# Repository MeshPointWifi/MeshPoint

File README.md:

# MeshPoint
MeshPoint is Open source Wifi Hotspot for Crisis Situations
www.meshpointone.com

## MeshPoint v4.1

## Technical Specifications

- **CPU / SoC:** 700 MHz Quad-core Cortex-A7 / Qualcomm IPQ4018
- **RAM memory and storage:** 128 MB NAND and 8 MB NOR flash, 256 MB DDR3 RAM
- **Wi-Fi standards:** 802.11 a/b/g/n/ac Wave 2
- **Mesh protocol:** 802.11s mesh networking protocol
- **Radio:** 2.4 GHz and 5 GHz dual band
- **MIMO:** 2.4 GHz 2x2 MIMO / 5.8 GHz 2x2 MIMO
- **VLAN:** 802.1Q VLAN
- **Monitoring:** SNMP v2 / SNMP v3
- **Environment:** Indoor / Outdoor
- **Concurrent clients:** 300+
- **PoE mode:** Passive PoE in and PoE out
- **Power supply:** Battery powered, solar powered or PoE in
- **Antennas:** Internal dual-band antennas, 7 dBi
- **Wireless security:** WEP, WPA-PSK, WPA-Enterprise (WPA/WPA2, TKIP/AES), WPA3
- **Power consumption:** Average 4 W, maximum 12 W
- **Maximum TX power:** 20 dBm
- **Operating temperature:** -40 °C to 70 °C (-40 °F to 158 °F)
- **Licence:** Free
- **Available interfaces:** USB 2.0, USB 3.0, I2C, I2S, TDM, SPI, UART, GPIO, JTAG
- **Network ports:** 2x 1000BASE-T Ethernet ports
- **LTE modem option:** USB LTE Cat 4 modem

## New features

- [x] PoE Passtrough ( IN + OUT - daisy-chain )
- [x] On board sensor PRESSURE HUMIDITY TEMP
- [x] PCF8563T - on board RTC

## Licence

This project (hardware designs, 3D files and documentation) is released under the
**CERN Open Hardware Licence Version 2 - Strongly Reciprocal (CERN-OHL-S v2)**.

See the [LICENCE](LICENCE) file for the full text.
More info: https://cern-ohl.web.cern.ch/

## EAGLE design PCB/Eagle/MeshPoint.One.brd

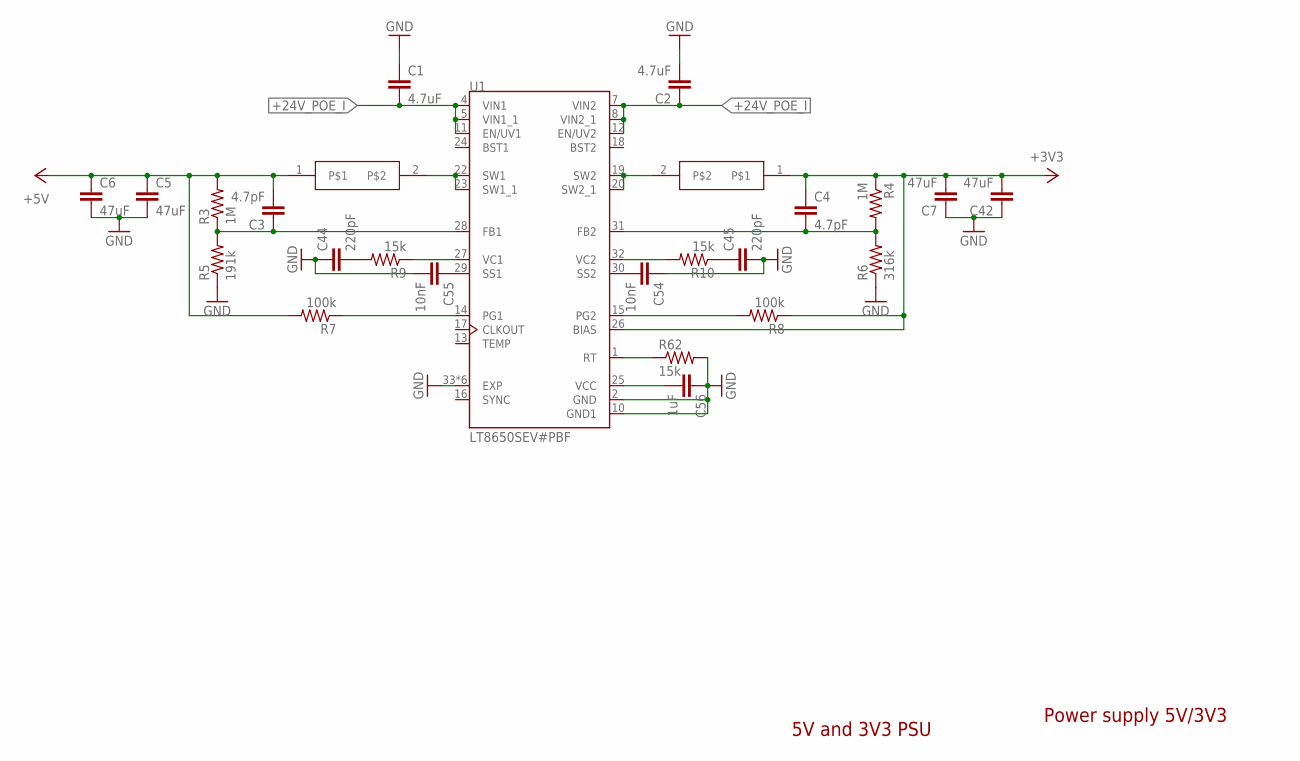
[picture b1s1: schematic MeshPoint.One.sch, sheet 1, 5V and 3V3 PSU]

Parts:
C1, C2: 4.7uF; C1206
C3, C4: 4.7pF; C0402
C5, C6, C7, C42: 47uF; C1206
C44, C45: 220pF; C0402
C54, C55: 10nF; C0402
C56: 1uF; C0402
L1, L2: PA4333.102NLTPA4333.102NLT; INDC6932X320
R3, R4: 1M; R0402
R5: 191k; R0402
R6: 316k; R0402
R7, R8: 100k; R0402
R9, R10, R62: 15k; R0402
U1: LT8650SEV#PBF; QFN50P600X400X103-32N240X440

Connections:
+24V_POE_I: C1.2, C2.1, U1.4 (VIN1), U1.5 (VIN1_1), U1.7 (VIN2), U1.8 (VIN2_1), U1.11 (EN/UV1), U1.12 (EN/UV2); also elsewhere on the board
GND: C1.1, C2.2, C5.2, C6.2, C7.1, C42.1, C44.1, C45.2, C54.1, C55.2, C56.1, R5.1, R6.1, R62.2, U1.2 (GND), U1.10 (GND1), U1.33 (EXP), U1.34 (EXP), U1.35 (EXP), U1.36 (EXP), U1.37 (EXP), U1.38 (EXP); also elsewhere on the board
unnamed: L1.2, U1.22 (SW1), U1.23 (SW1_1)
unnamed: L2.2, U1.19 (SW2), U1.20 (SW2_1)
unnamed: C3.1, R3.1, R5.2, U1.28 (FB1)
unnamed: C4.2, R4.2, R6.2, U1.31 (FB2)
unnamed: C55.1, U1.29 (SS1)
unnamed: R7.1, U1.14 (PG1)
unnamed: R8.2, U1.15 (PG2)
unnamed: C54.2, U1.30 (SS2)
unnamed: C44.2, R9.2
unnamed: C45.1, R10.1
unnamed: R9.1, U1.27 (VC1)
unnamed: R10.2, U1.32 (VC2)
unnamed: R62.1, U1.1 (RT)
unnamed: C56.2, U1.25 (VCC)
unnamed 153: C4.1, C7.2, C42.2, L2.1, R4.1, R8.1, U1.26 (BIAS); also elsewhere on the board
unnamed 184: C3.2, C5.1, C6.1, L1.1, R3.2, R7.2; also elsewhere on the board

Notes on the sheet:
Power supply 5V/3V3
5V and 3V3 PSU

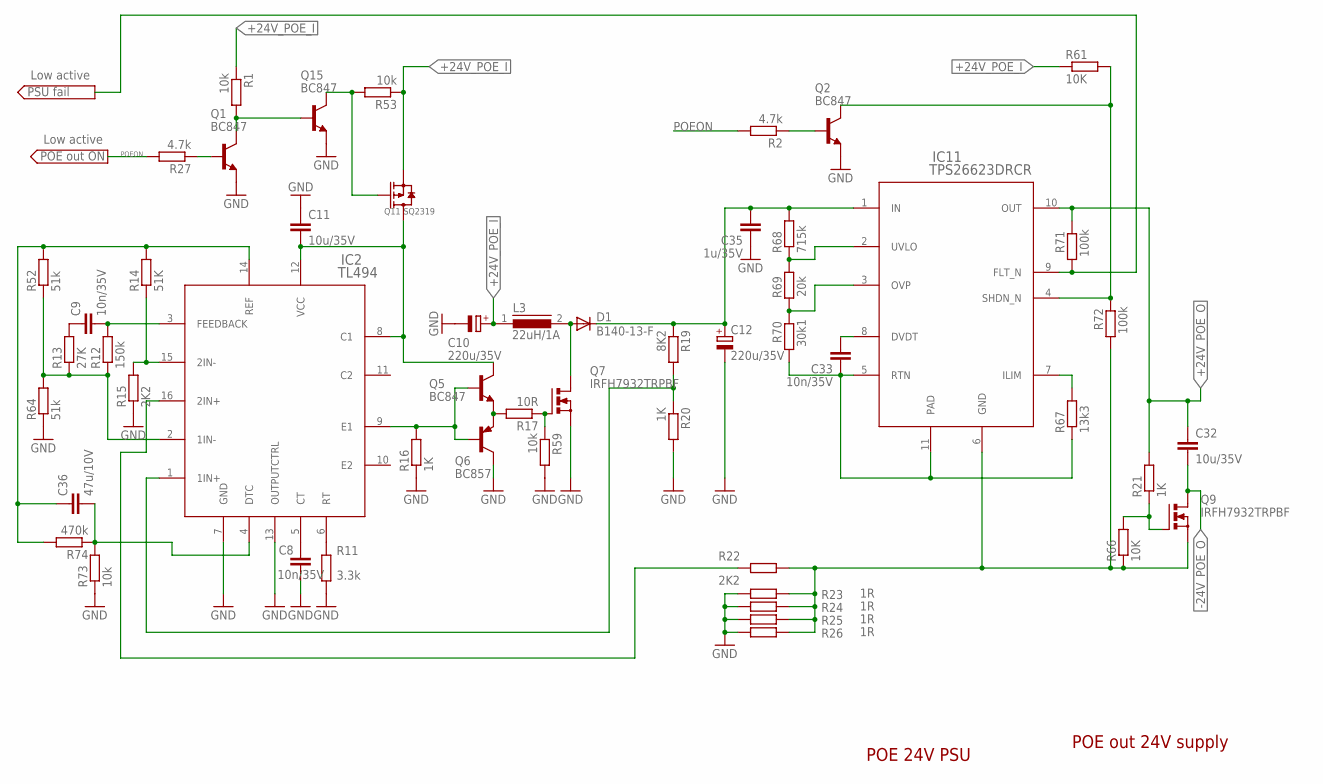
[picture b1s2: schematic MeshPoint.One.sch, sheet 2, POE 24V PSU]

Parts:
C8, C9, C33: 10n/35V; C0402
C10, C12: 220u/35V; 153CLV-1010
C11, C32: 10u/35V; C1206
C35: 1u/35V; C0402
C36: 47u/10V; C1206
D1: B140-13-F; SMB
IC2: TL494; PW16
IC11: TPS26623DRCR; DRC0010J
L3: 22uH/1A; DR125
Q1, Q2, Q5, Q15: BC847; SOT23
Q6: BC857; SOT23-BEC
Q7, Q9: IRFH7932TRPBF; PG-TDSON-8
Q11: SQ2319; SOT-23:1
R1, R53, R59, R73: 10k; R0402
R2, R27: 4.7k; R0402
R11: 3.3k; R0402
R12: 150k; R0402
R13: 27K; R0402
R14: 51K; R0402
R15, R22: 2K2; R0402
R16, R20, R21: 1K; R0402
R17: 10R; R0402
R19: 8K2; R0402
R23, R24, R25, R26: 1R; M1206
R52, R64: 51k; R0402
R61, R66: 10K; R0402
R67: 13k3; R0402
R68: 715k; R0402
R69: 20k; R0402
R70: 30k1; R0402
R71, R72: 100k; R0402
R74: 470k; R0402

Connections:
+24V_POE_I: C10.+, L3.1, Q11.2 (S), R1.1, R53.1, R61.1; also elsewhere on the board
+24V_POE_O: C32.1, IC11.10 (OUT), R21.2, R71.2; also elsewhere on the board
-24V_POE_O: C32.2, Q9.5 (D), Q9.6 (D), Q9.7 (D), Q9.8 (D), Q9.TH (D); also elsewhere on the board
GND: C8.2, C10.-, C11.1, C12.-, C35.1, IC2.7 (GND), IC2.13 (OUTPUTCTRL), Q1.2 (E), Q2.2 (E), Q6.C, Q7.1 (S), Q7.2 (S), Q7.3 (S), Q15.2 (E), R11.1, R15.1, R16.1, R20.2, R23.1, R24.1, R25.1, R26.1, R59.2, R64.1, R73.1; also elsewhere on the board
unnamed: IC2.6 (RT), R11.2
unnamed: C8.1, IC2.5 (CT)
unnamed: C36.2, IC2.4 (DTC), R73.2, R74.1
unnamed: C9.2, IC2.3 (FEEDBACK), R12.2
unnamed: Q1.1 (B), R27.1
unnamed: IC2.15 (2IN-), R14.1, R15.2
unnamed: IC2.9 (E1), Q5.1 (B), Q6.B, R16.2
unnamed: Q5.2 (E), Q6.E, R17.2
unnamed: C36.1, IC2.14 (REF), R14.2, R52.2, R74.2
unnamed: Q7.4 (G), R17.1, R59.1
unnamed: IC2.1 (1IN+), R19.2, R20.1
unnamed: C33.2, IC11.8 (DVDT)
unnamed: IC2.16 (2IN+), R22.1
unnamed: Q1.3 (C), Q15.1 (B), R1.2
unnamed: Q2.1 (B), R2.1
unnamed: C9.1, R13.2
unnamed: IC11.4 (SHDN_N), Q2.3 (C), R61.2, R72.2
unnamed: C12.+, C35.2, D1.C, IC11.1 (IN), R19.1, R68.2
unnamed: Q11.1 (G), Q15.3 (C), R53.2
unnamed: C11.2, IC2.8 (C1), IC2.12 (VCC), Q5.3 (C), Q11.3 (D)
unnamed: Q9.4 (G), R21.1, R66.2
unnamed: IC11.7 (ILIM), R67.2
unnamed: D1.A, L3.2, Q7.5 (D), Q7.6 (D), Q7.7 (D), Q7.8 (D), Q7.TH (D)
unnamed: C33.1, IC11.5 (RTN), IC11.11 (PAD), R67.1, R70.1
unnamed: IC11.6 (GND), Q9.1 (S), Q9.2 (S), Q9.3 (S), R22.2, R23.2, R24.2, R25.2, R26.2, R66.1, R72.1
unnamed: IC2.2 (1IN-), R12.1, R13.1, R52.1, R64.2
unnamed: IC11.2 (UVLO), R68.1, R69.2
unnamed: IC11.3 (OVP), R69.1, R70.2
POEON: R2.2, R27.2; also elsewhere on the board
PSU_FAIL: IC11.9 (FLT_N), R71.1

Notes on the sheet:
POE out 24V supply
POE 24V PSU
Low active

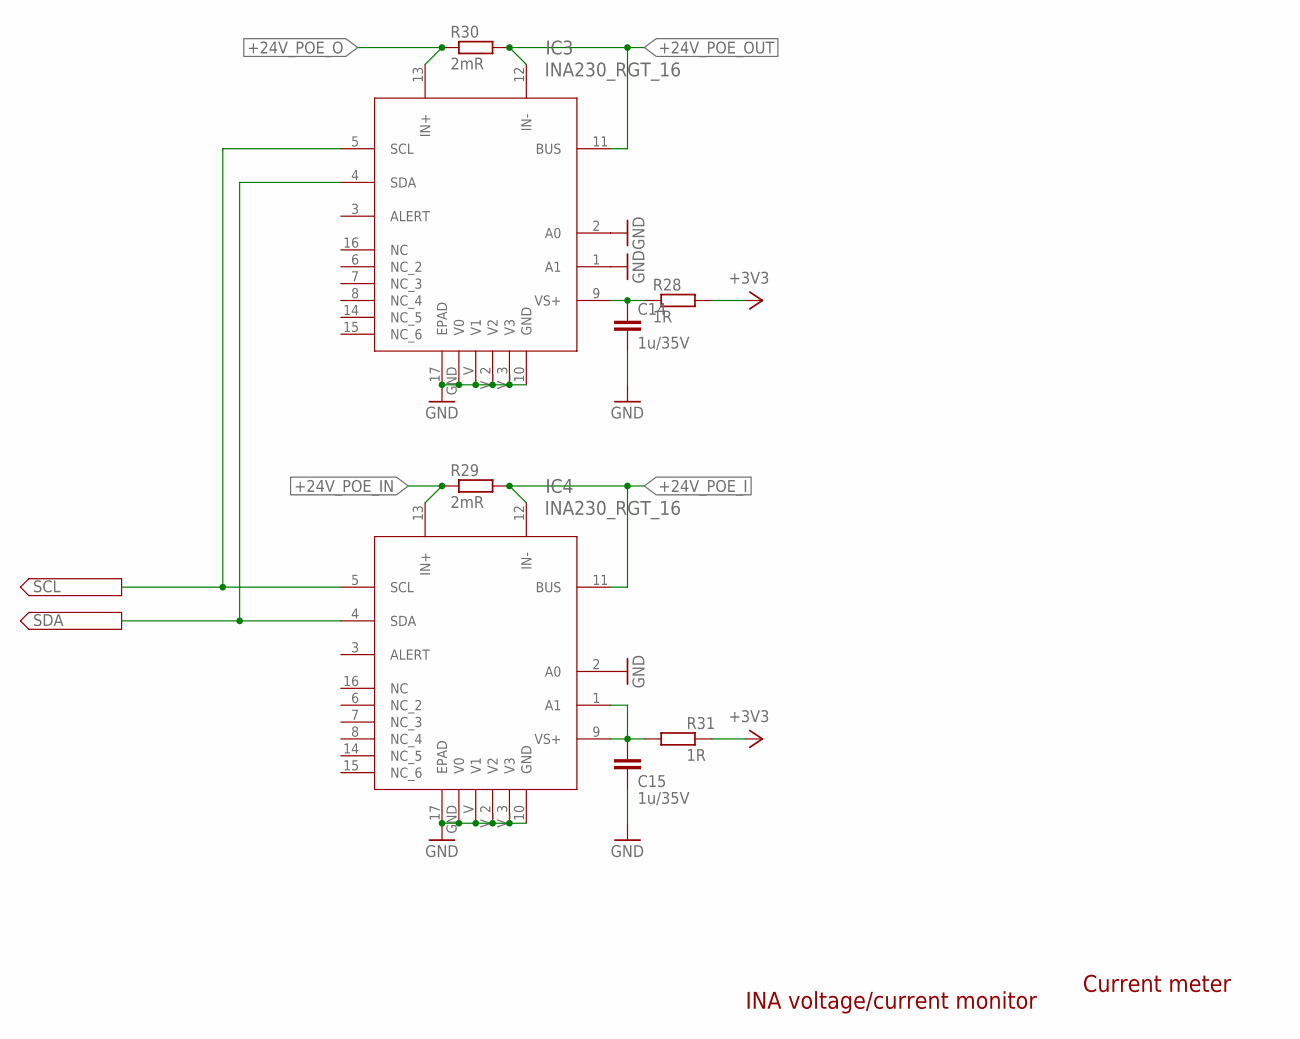
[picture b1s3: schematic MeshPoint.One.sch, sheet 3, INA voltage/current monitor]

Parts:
C14, C15: 1u/35V; C0402
IC3, IC4: INA230_RGT_16; RGT16_1P7X1P7
R28, R31: 1R; R0402
R29, R30: 2mR; M1206

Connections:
+24V_POE_I: IC4.11 (BUS), IC4.12 (IN-), R29.2; also elsewhere on the board
+24V_POE_IN: IC4.13 (IN+), R29.1; also elsewhere on the board
+24V_POE_O: IC3.13 (IN+), R30.1; also elsewhere on the board
+24V_POE_OUT: IC3.11 (BUS), IC3.12 (IN-), R30.2; also elsewhere on the board
GND: C14.2, C15.2, IC3.1 (A1), IC3.2 (A0), IC3.10 (GND), IC3.17 (EPAD), IC3.GND (V0), IC3.V (V1), IC3.V_2 (V2), IC3.V_3 (V3), IC4.2 (A0), IC4.10 (GND), IC4.17 (EPAD), IC4.GND (V0), IC4.V (V1), IC4.V_2 (V2), IC4.V_3 (V3); also elsewhere on the board
unnamed: C14.1, IC3.9 (VS+), R28.1
unnamed: C15.1, IC4.1 (A1), IC4.9 (VS+), R31.1
unnamed 153: R28.2, R31.2; also elsewhere on the board
SCL: IC3.5 (SCL), IC4.5 (SCL); also elsewhere on the board
SDA: IC3.4 (SDA), IC4.4 (SDA); also elsewhere on the board

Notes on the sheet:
Current meter
INA voltage/current monitor

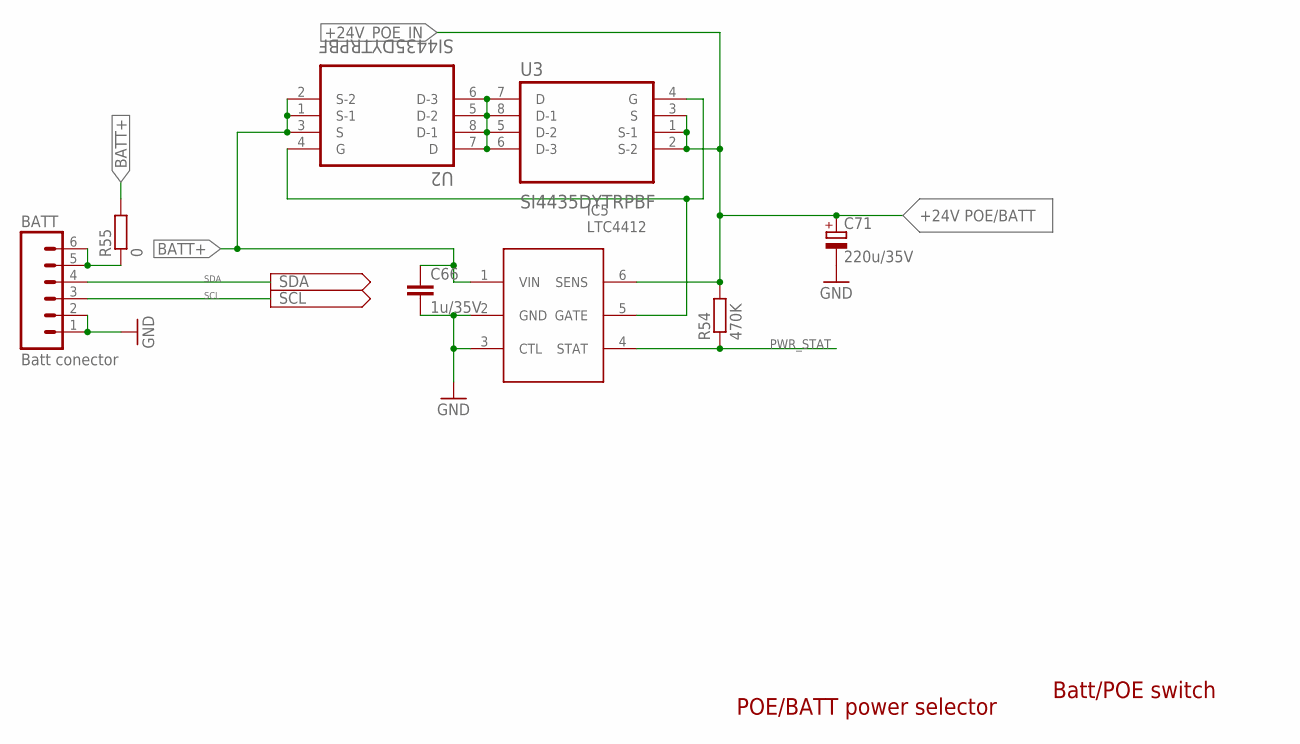
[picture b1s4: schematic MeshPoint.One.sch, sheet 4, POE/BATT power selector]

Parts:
BATT: Batt conector; 06P
C66: 1u/35V; C0402
C71: 220u/35V; 153CLV-1010
IC5: LTC4412; TSOT23
R54: 470K; R0402
R55: 0; M0805
U2, U3: SI4435DYTRPBF; SOIC127P490X600X175-8N

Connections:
+24V_POE_IN: C71.+, IC5.6 (SENS), R54.2, U3.1 (S-1), U3.2 (S-2), U3.3 (S); also elsewhere on the board
BATT+: C66.1, IC5.1 (VIN), R55.2, U2.1 (S-1), U2.2 (S-2), U2.3 (S)
GND: BATT.1, BATT.2, C66.2, C71.-, IC5.2 (GND), IC5.3 (CTL); also elsewhere on the board
unnamed: U2.5 (D-2), U2.6 (D-3), U2.7 (D), U2.8 (D-1), U3.5 (D-2), U3.6 (D-3), U3.7 (D), U3.8 (D-1)
unnamed: IC5.5 (GATE), U2.4 (G), U3.4 (G)
unnamed: BATT.5, BATT.6, R55.1
PWR_STAT: IC5.4 (STAT), R54.1
SCL: BATT.3; also elsewhere on the board
SDA: BATT.4; also elsewhere on the board

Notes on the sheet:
Batt/POE switch
POE/BATT power selector
+24V POE/BATT

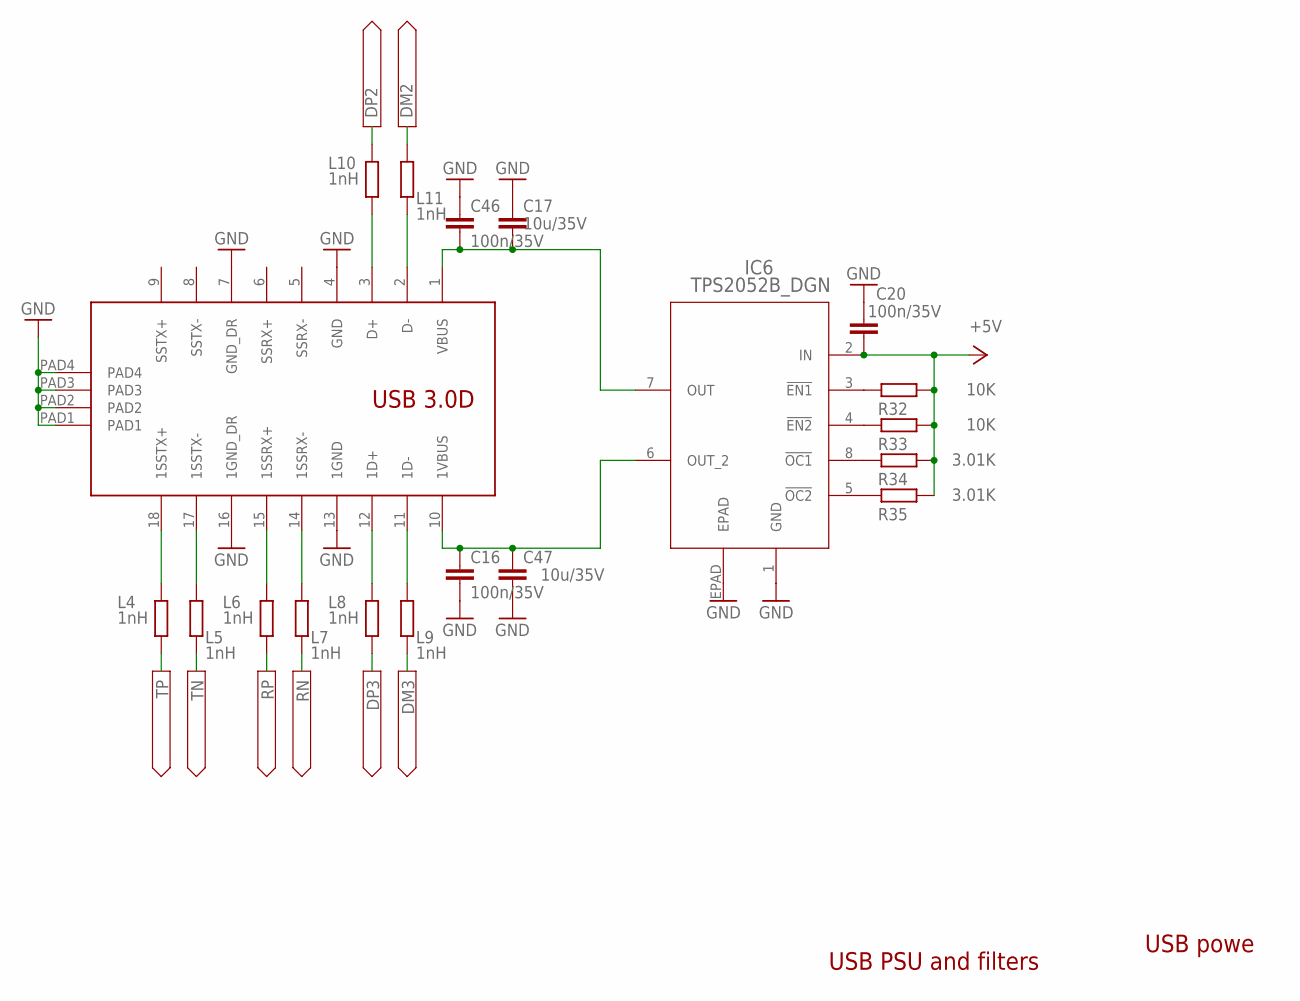
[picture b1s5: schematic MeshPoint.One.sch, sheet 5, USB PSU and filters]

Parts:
C16, C20, C46: 100n/35V; C0402
C17, C47: 10u/35V; C1206
IC6: TPS2052B_DGN; DGN8_1P89X1P57
L4, L5, L6, L7, L8, L9, L10, L11: 1nH; R0402
R32, R33: 10K; R0402
R34, R35: 3.01K; R0402
USB3.0: USB3.0D

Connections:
DM2: L11.1; also elsewhere on the board
DM3: L9.2; also elsewhere on the board
DP2: L10.1; also elsewhere on the board
DP3: L8.2; also elsewhere on the board
GND: C16.2, C17.1, C20.1, C46.1, C47.2, IC6.1 (GND), IC6.EPAD, USB3.0.4 (GND), USB3.0.7 (GND_DR), USB3.0.13 (1GND), USB3.0.16 (1GND_DR), USB3.0.PAD1, USB3.0.PAD2, USB3.0.PAD3, USB3.0.PAD4; also elsewhere on the board
unnamed: L4.1, USB3.0.18 (1SSTX+)
unnamed: L5.1, USB3.0.17 (1SSTX-)
unnamed: L6.1, USB3.0.15 (1SSRX+)
unnamed: L7.1, USB3.0.14 (1SSRX-)
unnamed: L8.1, USB3.0.12 (1D+)
unnamed: L9.1, USB3.0.11 (1D-)
unnamed: IC6.3 (!EN1), R32.2
unnamed: IC6.4 (!EN2), R33.2
unnamed: IC6.8 (!OC1), R34.2
unnamed: IC6.5 (!OC2), R35.2
unnamed: C16.1, C47.1, IC6.6 (OUT_2), USB3.0.10 (1VBUS)
unnamed: L10.2, USB3.0.3 (D+)
unnamed: L11.2, USB3.0.2 (D-)
unnamed: C17.2, C46.2, IC6.7 (OUT), USB3.0.1 (VBUS)
unnamed 184: C20.2, IC6.2 (IN), R32.1, R33.1, R34.1, R35.1; also elsewhere on the board
RN: L7.2; also elsewhere on the board
RP: L6.2; also elsewhere on the board
TN: L5.2; also elsewhere on the board
TP: L4.2; also elsewhere on the board

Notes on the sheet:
USB powe
USB PSU and filters

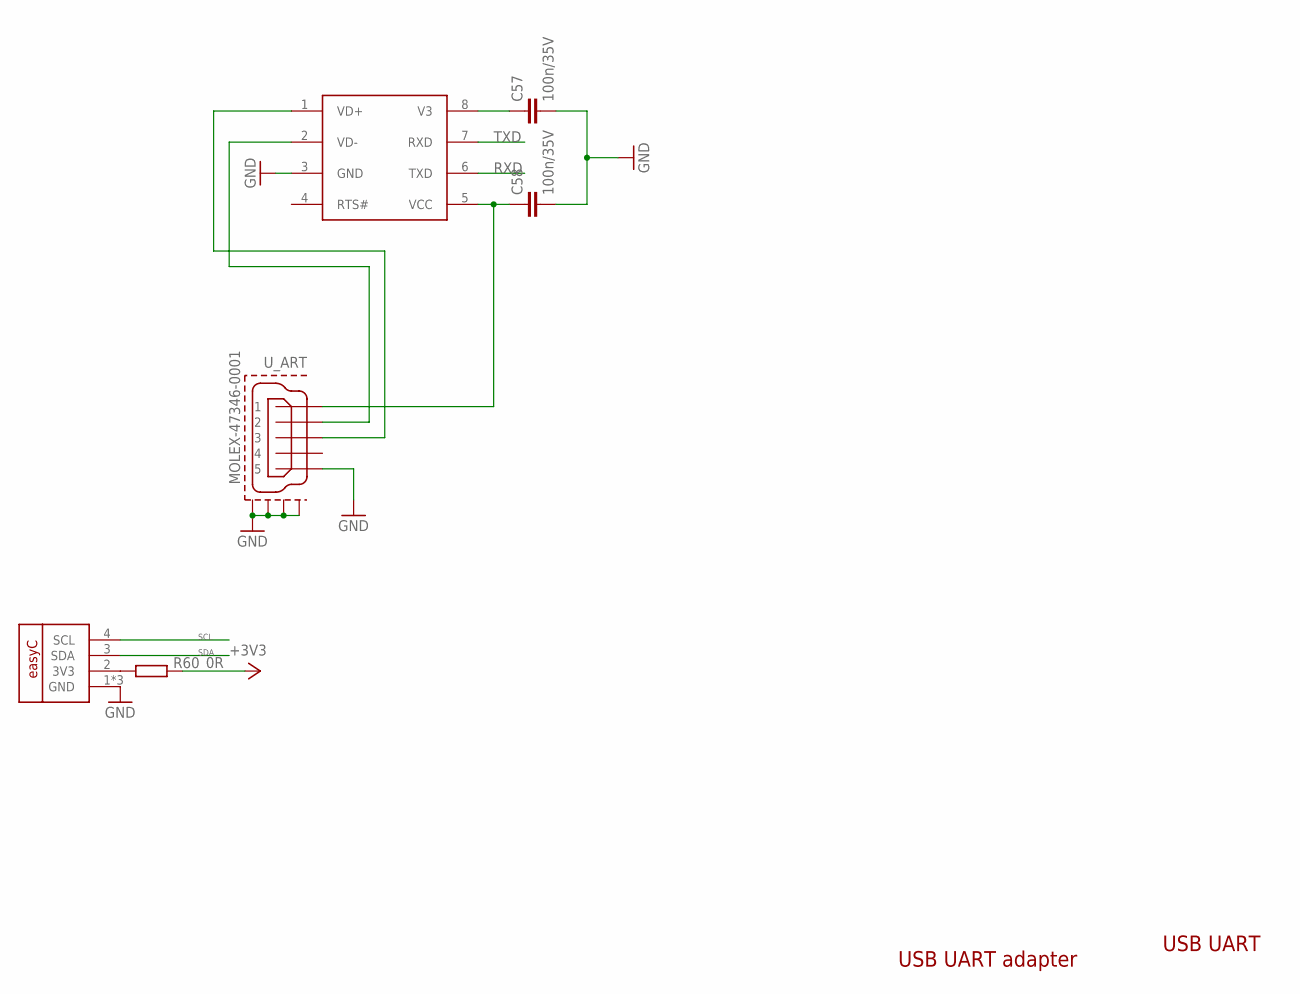
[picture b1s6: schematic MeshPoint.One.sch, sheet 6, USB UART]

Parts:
C57, C58: 100n/35V; C0402
CN2: EASYC
IC10: CH330N; SOIC127P600X175-8
R60: 0R; R0805
U_ART: MOLEX-47346-0001; MOLEX-47364-0001

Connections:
GND: C57.2, C58.2, CN2.1 (GND), CN2.NC1 (GND), CN2.NC2 (GND), IC10.3 (GND), U_ART.5, U_ART.GND1, U_ART.GND2, U_ART.GND3, U_ART.GND4; also elsewhere on the board
unnamed: C57.1, IC10.8 (V3)
unnamed: C58.1, IC10.5 (VCC), U_ART.1
unnamed 153: R60.2; also elsewhere on the board
unnamed: CN2.2 (3V3), R60.1
unnamed: IC10.2 (VD-), U_ART.2
unnamed: IC10.1 (VD+), U_ART.3
RXD: IC10.6 (TXD); also elsewhere on the board
SCL: CN2.4 (SCL); also elsewhere on the board
SDA: CN2.3 (SDA); also elsewhere on the board
TXD: IC10.7 (RXD); also elsewhere on the board

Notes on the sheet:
USB UART
USB UART adapter

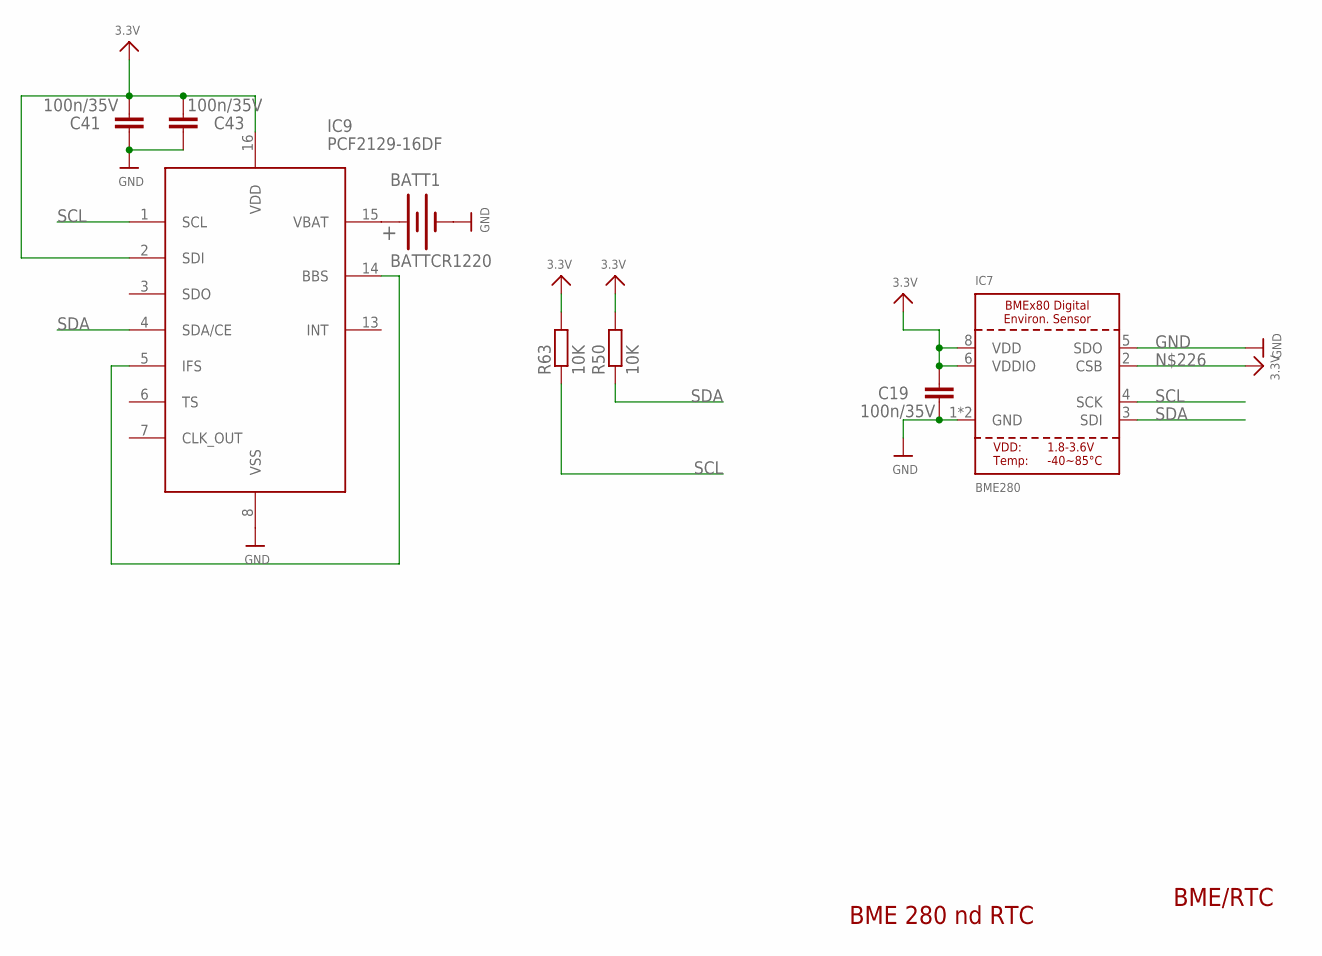
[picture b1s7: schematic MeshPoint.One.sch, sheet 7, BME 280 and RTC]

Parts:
BATT1: BATTCR1220; BATERIJA12MM
C19, C41, C43: 100n/35V; C0402
IC7: BME280
IC9: PCF2129-16DF; SO16DF
R50, R63: 10K; R0402

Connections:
GND: BATT1.-, C19.2, C41.1, C43.1, IC7.1 (GND), IC7.5 (SDO), IC7.7 (GND), IC9.8 (VSS); also elsewhere on the board
unnamed: BATT1.+, IC9.15 (VBAT)
unnamed 153: C19.1, C41.2, C43.2, IC7.2 (CSB), IC7.6 (VDDIO), IC7.8 (VDD), IC9.2 (SDI), IC9.16 (VDD), R50.2, R63.2; also elsewhere on the board
unnamed: IC9.5 (IFS), IC9.14 (BBS)
SCL: IC7.4 (SCK), IC9.1 (SCL), R63.1; also elsewhere on the board
SDA: IC7.3 (SDI), IC9.4 (SDA/CE), R50.1; also elsewhere on the board

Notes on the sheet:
BME/RTC
BME 280 nd RTC

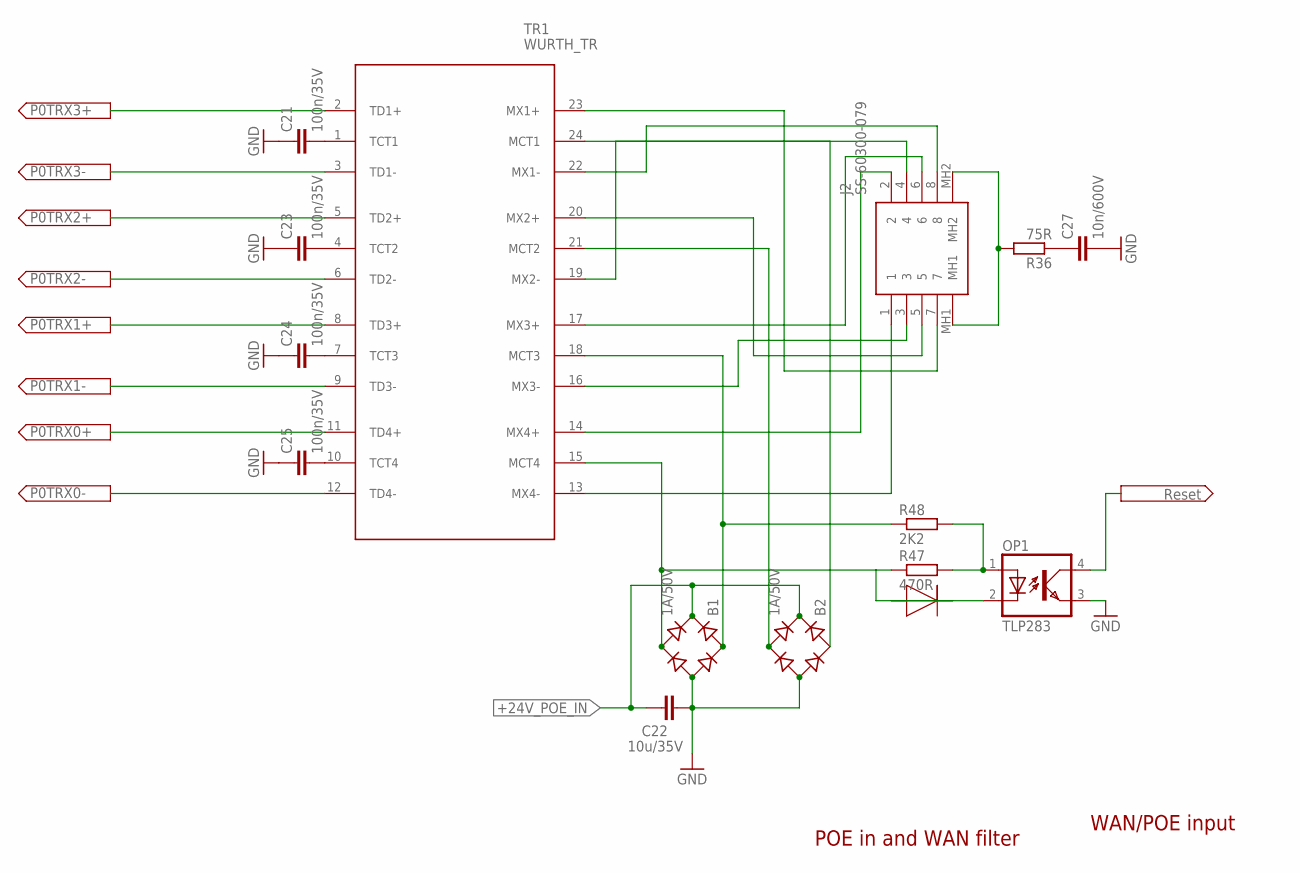
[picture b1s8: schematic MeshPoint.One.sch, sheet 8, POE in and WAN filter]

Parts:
B1, B2: 1A/50V; MBS
C21, C23, C24, C25: 100n/35V; C0402
C22: 10u/35V; C1206
C27: 10n/600V; C1206K
J2: SS-60300-079; SS60300079
OP1: TLP283; MINI-FLAT-4
R36: 75R; M1206
R47: 470R; R0402
R48: 2K2; R0402
TR1: WURTH_TR; WURTH1000T
ZD3: BZT52C15S; SOD2513X120N

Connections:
+24V_POE_IN: B1.+, B2.+, C22.1; also elsewhere on the board
GND: B1.-, B2.-, C21.1, C22.2, C23.1, C24.1, C25.1, C27.2, OP1.3 (EMIT); also elsewhere on the board
unnamed: J2.2, TR1.14 (MX4+)
unnamed: J2.6, TR1.17 (MX3+)
unnamed: J2.4, TR1.19 (MX2-)
unnamed: J2.5, TR1.20 (MX2+)
unnamed: J2.3, TR1.16 (MX3-)
unnamed: J2.7, TR1.23 (MX1+)
unnamed: OP1.1 (A), R47.2, R48.2
unnamed: J2.8, TR1.22 (MX1-)
unnamed: J2.MH1, J2.MH2, R36.2
unnamed: B1.AC1, R48.1, TR1.18 (MCT3)
unnamed: B2.AC2, TR1.21 (MCT2)
unnamed: C27.1, R36.1
unnamed: OP1.2 (C), ZD3.A
unnamed: C21.2, TR1.1 (TCT1)
unnamed: C23.2, TR1.4 (TCT2)
unnamed: C24.2, TR1.7 (TCT3)
unnamed: C25.2, TR1.10 (TCT4)
unnamed: B2.AC1, TR1.24 (MCT1)
unnamed: J2.1, TR1.13 (MX4-)
unnamed: B1.AC2, R47.1, TR1.15 (MCT4), ZD3.C
P0TRX0+: TR1.11 (TD4+); also elsewhere on the board
P0TRX0-: TR1.12 (TD4-); also elsewhere on the board
P0TRX1+: TR1.8 (TD3+); also elsewhere on the board
P0TRX1-: TR1.9 (TD3-); also elsewhere on the board
P0TRX2+: TR1.5 (TD2+); also elsewhere on the board
P0TRX2-: TR1.6 (TD2-); also elsewhere on the board
P0TRX3+: TR1.2 (TD1+); also elsewhere on the board
P0TRX3-: TR1.3 (TD1-); also elsewhere on the board
RESET: OP1.4 (COL); also elsewhere on the board

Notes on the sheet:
WAN/POE input
POE in and WAN filter

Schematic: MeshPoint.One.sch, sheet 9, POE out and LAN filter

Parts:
B3, B4: 1A/50V; MBS
C26, C29, C30, C31: 100n/35V; C0402
C28: 10n/600V; C1206K
C34: 10u/35V; C1206
F1: 2A; PTC1812L
J1: SS-60300-079; SS60300079
R37: 75R; M1206
TR2: WURTH_TR; WURTH1000T

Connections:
+24V_POE_OUT: F1.1; also elsewhere on the board
-24V_POE_O: B3.AC2, B4.AC2, C34.2; also elsewhere on the board
GND: C26.1, C28.2, C29.1, C30.1, C31.1; also elsewhere on the board
unnamed: B4.+, TR2.21 (MCT2)
unnamed: J1.1, TR2.13 (MX4-)
unnamed: J1.2, TR2.14 (MX4+)
unnamed: J1.3, TR2.16 (MX3-)
unnamed: C28.1, R37.1
unnamed: J1.4, TR2.19 (MX2-)
unnamed: J1.5, TR2.20 (MX2+)
unnamed: J1.6, TR2.17 (MX3+)
unnamed: J1.7, TR2.23 (MX1+)
unnamed: J1.8, TR2.22 (MX1-)
unnamed: J1.MH1, J1.MH2, R37.2
unnamed: C26.2, TR2.1 (TCT1)
unnamed: C29.2, TR2.4 (TCT2)
unnamed: C30.2, TR2.7 (TCT3)
unnamed: C31.2, TR2.10 (TCT4)
unnamed: B3.+, TR2.15 (MCT4)
unnamed: B3.AC1, B4.AC1, C34.1, F1.2
unnamed: B3.-, TR2.18 (MCT3)
unnamed: B4.-, TR2.24 (MCT1)
P1TRX0+: TR2.11 (TD4+); also elsewhere on the board
P1TRX0-: TR2.12 (TD4-); also elsewhere on the board
P1TRX1+: TR2.8 (TD3+); also elsewhere on the board
P1TRX1-: TR2.9 (TD3-); also elsewhere on the board
P1TRX2+: TR2.5 (TD2+); also elsewhere on the board
P1TRX2-: TR2.6 (TD2-); also elsewhere on the board
P1TRX3+: TR2.2 (TD1+); also elsewhere on the board
P1TRX3-: TR2.3 (TD1-); also elsewhere on the board

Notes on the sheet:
LAN/POE out
POE out and LAN filter

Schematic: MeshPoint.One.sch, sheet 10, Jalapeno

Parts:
3V3, 5V, 1000A, 1000B: GR; CHIP-LED0603
100A, 100B: YL; CHIP-LED0603
C13, C18: 100p/35V; C0402
C37, C38, C39: 100n; C0402
C40: 100n/35V; C0402
FD1, FD2, FD3, FD4, FD5: FIDUCIALUFIDUCIAL; FIDUCIAL-MICRO
LED: MOMENTARY-SWITCH-SPST-SMD-4.6X2.8MM; TACTILE_SWITCH_SMD_4.6X2.8MM
PW_DN: PW_DN; TACTILE_SWITCH_SMD_4.6X2.8MM
R38, R39, R40, R41, R43: 330R; R0402
R42, R44: 470R; R0402
R45: 10k; R0402
R46: 2K2; R0402
R49, R51: 4K7; R0402
R65: 0; M0805
RST: RST; TACTILE_SWITCH_SMD_4.6X2.8MM
STATUS: BL; CHIP-LED0603
U$5: JALAPENO; JALAPENO-PCB
U$9: HEATSINK
VIN: GR; CHIP-LED0603
VOUT: BL; CHIP-LED0603

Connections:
+24V_POE_I: R46.2; also elsewhere on the board
+24V_POE_O: R45.2; also elsewhere on the board
-24V_POE_O: VOUT.C; also elsewhere on the board
DM2: U$5.11 (USB2DM); also elsewhere on the board
DM3: U$5.20 (USB3DM); also elsewhere on the board
DP2: U$5.12 (USB2DP); also elsewhere on the board
DP3: U$5.21 (USB3DP); also elsewhere on the board
GND: C13.1, C18.2, C37.2, C38.2, C39.2, C40.2, LED.3 (2), LED.4 (2), PW_DN.3 (2), PW_DN.4 (2), R65.2, RST.3 (2), RST.4 (2), U$5.1 (GND), U$5.10 (GND10), U$5.13 (GND13), U$5.16 (GND16), U$5.19 (GND19), U$5.22 (GND22), U$5.28 (GND28), U$5.29 (GND29), U$5.30 (GND30), U$5.31 (GND31), U$5.32 (GND32), U$5.33 (GND33), U$5.34 (GND34), U$5.35 (GND35), U$5.37 (GND37), U$5.41 (GND41), U$5.45 (GND45), U$5.47 (GND47), U$5.50 (GND50), U$5.51 (GND51), U$5.53 (GND53), U$5.54 (GND54), U$5.56 (GND56), U$5.58 (GND58); also elsewhere on the board
GPIO63: R42.2, U$5.25 (GPIO59)
LED_GND: 3V3.C, 5V.C, 100A.C, 100B.C, 1000A.C, 1000B.C, LED.1, LED.2 (1), R65.1, STATUS.C, VIN.C
unnamed: 100A.A, R38.1
unnamed: 1000A.A, R39.1
unnamed: 100B.A, R40.1
unnamed: 1000B.A, R41.1
unnamed: R42.1, STATUS.A
unnamed: 3V3.A, R43.1
unnamed: 5V.A, R44.1
unnamed: R45.1, VOUT.A
unnamed: R46.1, VIN.A
unnamed 153: C37.1, C38.1, C39.1, C40.1, R43.2, R49.1, R51.2, U$5.23 (3V3_23), U$5.36 (3V3_36), U$5.49 (3V3_49), U$5.57 (3V3_57); also elsewhere on the board
unnamed 184: R44.2; also elsewhere on the board
P0TRX0+: U$5.63 (P0TRX0+); also elsewhere on the board
P0TRX0-: U$5.64 (P0TRX0-); also elsewhere on the board
P0TRX1+: U$5.65 (P0TRX1+); also elsewhere on the board
P0TRX1-: U$5.66 (P0TRX1-); also elsewhere on the board
P0TRX2+: U$5.67 (P0TRX2+); also elsewhere on the board
P0TRX2-: U$5.68 (P0TRX2-); also elsewhere on the board
P0TRX3+: U$5.69 (P0TRX3+); also elsewhere on the board
P0TRX3-: U$5.70 (P0TRX3-); also elsewhere on the board
P1TRX0+: U$5.2 (P1TRX0+); also elsewhere on the board
P1TRX0-: U$5.3 (P1TRX0-); also elsewhere on the board
P1TRX1+: U$5.4 (P1TRX1+); also elsewhere on the board
P1TRX1-: U$5.5 (P1TRX1-); also elsewhere on the board
P1TRX2+: U$5.6 (P1TRX2+); also elsewhere on the board
P1TRX2-: U$5.7 (P1TRX2-); also elsewhere on the board
P1TRX3+: U$5.8 (P1TRX3+); also elsewhere on the board
P1TRX3-: U$5.9 (P1TRX3-); also elsewhere on the board
P0100: R38.2, U$5.59 (P0_100_LED)
P01000: R39.2, U$5.61 (P0_1000_LED)
P1100: R40.2, U$5.60 (P1_100_LED)
P11000: R41.2, U$5.62 (P1_1000_LED)
POEON: U$5.38 (JTAG_TCK); also elsewhere on the board
PWD: C13.2, PW_DN.1, PW_DN.2 (1), R51.1, U$5.46 (CHIP_PWD)
RESET: C18.1, R49.2, RST.1, RST.2 (1), U$5.44 (JTAG_TRST); also elsewhere on the board
RN: U$5.18 (USB3RXN); also elsewhere on the board
RP: U$5.17 (USB3RXP); also elsewhere on the board
RXD: U$5.26 (UART_RX); also elsewhere on the board
SCL: U$5.43 (JTAG_RST); also elsewhere on the board
SDA: U$5.39 (JTAG_TDI); also elsewhere on the board
TN: U$5.15 (USB3TXN); also elsewhere on the board
TP: U$5.14 (USB3TXP); also elsewhere on the board
TXD: U$5.27 (UART_TX); also elsewhere on the board

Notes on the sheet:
JALAPENO
IC10
HT1
Jalapeno and LED monitors

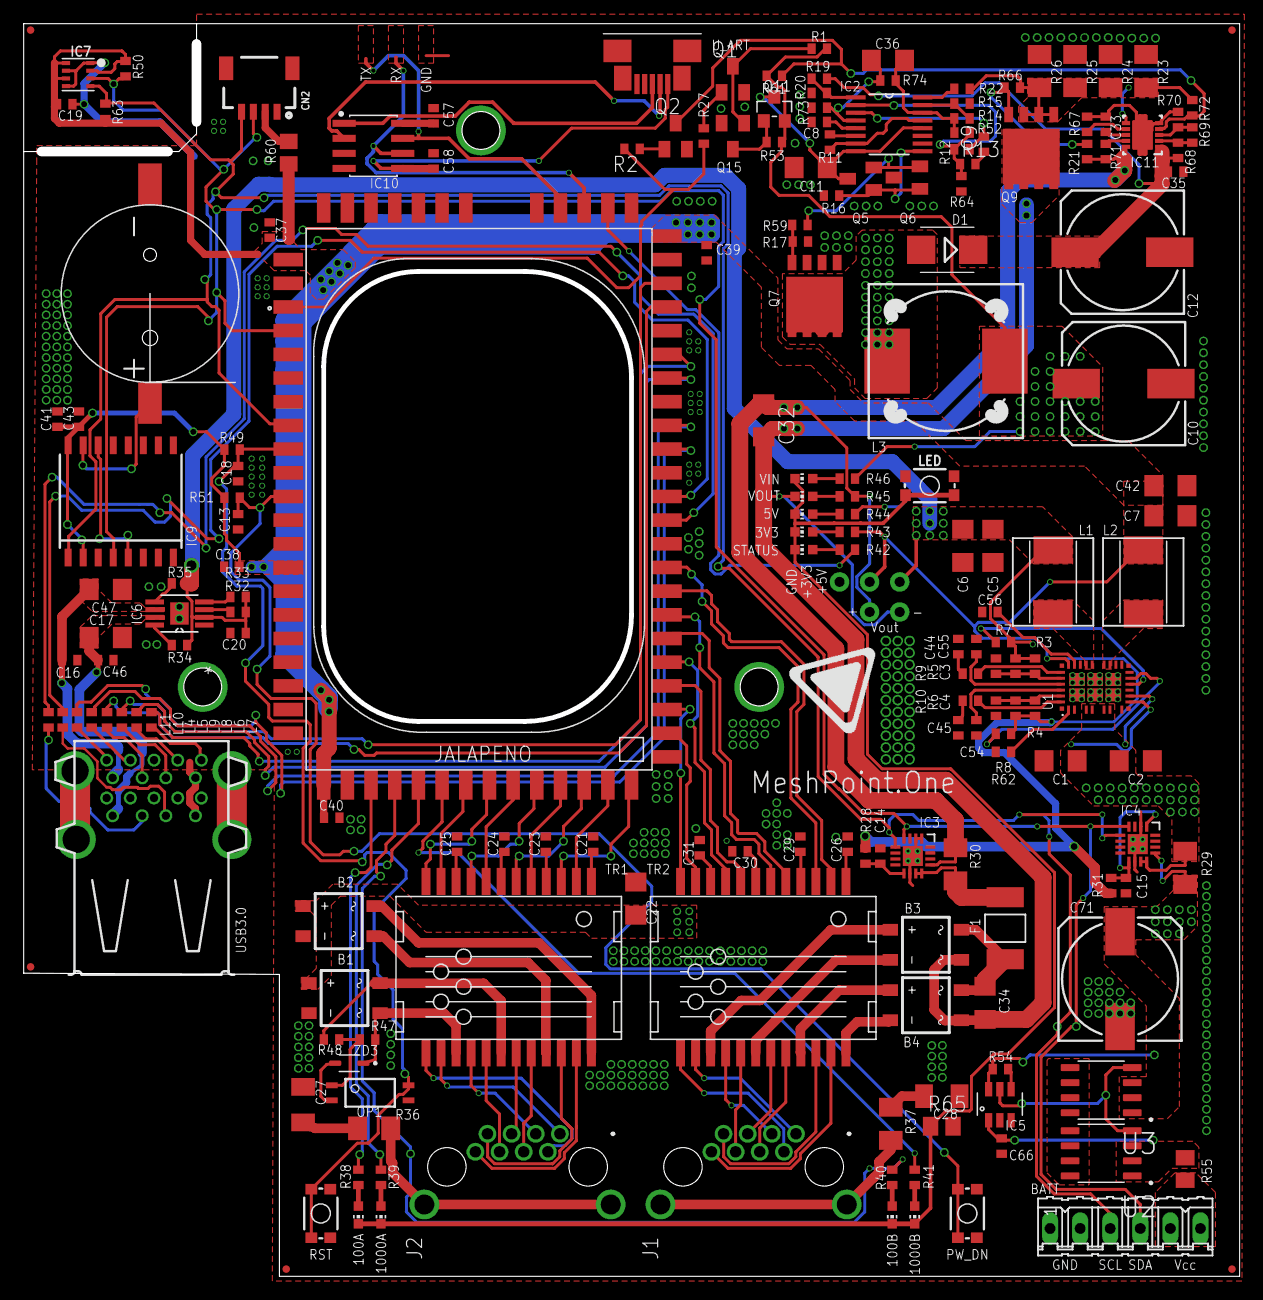
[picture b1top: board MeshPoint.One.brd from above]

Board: 2 copper layers, 101.9 x 105.0 mm, 191 parts (1 on the bottom side), 164 nets.

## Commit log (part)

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2017-01-27 Create LICENCE
2017-01-27 Added images
2017-01-27 renamed stl files
2017-05-22 added MeshPoint shell with MeshMixer supports added
2017-06-12 Removed nuts used for assembly, decreased hole diameter, reduced size of some parts for better fit.

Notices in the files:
parts and their libraries:
SparkFun-Switches: Licensing: Creative Commons ShareAlike 4.0 International - https://creativecommons.org/licenses/by-sa/4.0
